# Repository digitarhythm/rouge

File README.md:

# TReK Rouge
Analog joystick macropad with RP2040-Zero.

[Firmware repository](https://github.com/digitarhythm/vial-qmk/tree/digitarhythm/keyboards/trek/rouge)

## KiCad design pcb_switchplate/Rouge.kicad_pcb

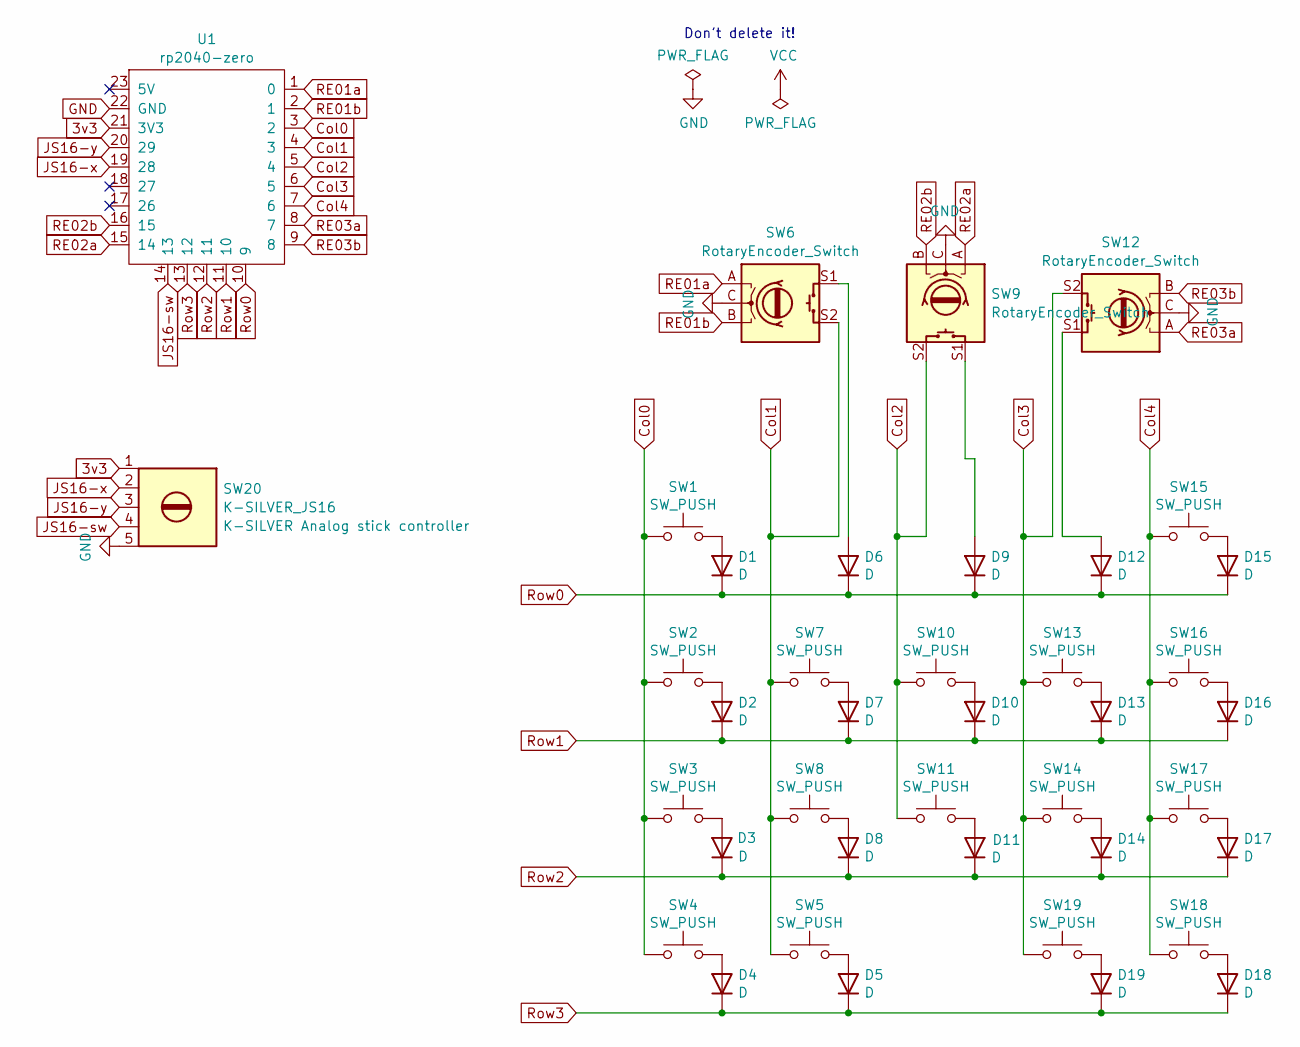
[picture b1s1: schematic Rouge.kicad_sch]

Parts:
D1, D2, D3, D4, D5, D6, D7, D8, D9, D10, D11, D12, D13, D14, D15, D16, D17, D18, D19: D; Diode_SMD
SW1, SW2, SW3, SW4, SW5, SW7, SW8, SW10, SW11, SW13, SW14, SW15, SW16, SW17, SW18, SW19: SW_PUSH; Lofree_Hotswap_1u(short_pad)
SW6, SW9, SW12: RotaryEncoder_Switch; RotaryEncoder_EC12E
SW20: K-SILVER_JS16; JS16
U1: rp2040-zero; rp2040-zero_rev(THonly)

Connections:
3v3: SW20.1, U1.21 (3V3)
Col0: SW1.1, SW2.1, SW3.1, SW4.1, U1.3 (2)
Col2: SW9.S2, SW10.1, SW11.1, U1.5 (4)
Col3: SW12.S2, SW13.1, SW14.1, SW19.1, U1.6 (5)
Col4: SW15.1, SW16.1, SW17.1, SW18.1, U1.7 (6)
GND: SW6.C, SW9.C, SW12.C, SW20.5, U1.22 (GND)
JS16-sw: SW20.4, U1.14 (13)
JS16-x: SW20.2, U1.19 (28)
JS16-y: SW20.3, U1.20 (29)
unnamed: D1.2 (A), SW1.2
unnamed: D2.2 (A), SW2.2
unnamed: D3.2 (A), SW3.2
unnamed: D4.2 (A), SW4.2
unnamed: D5.2 (A), SW5.2
unnamed: D6.2 (A), SW6.S1
unnamed: D7.2 (A), SW7.2
unnamed: D9.2 (A), SW9.S1
unnamed: D10.2 (A), SW10.2
unnamed: D11.2 (A), SW11.2
unnamed: D12.2 (A), SW12.S1
unnamed: D13.2 (A), SW13.2
unnamed: D14.2 (A), SW14.2
unnamed: D15.2 (A), SW15.2
unnamed: D16.2 (A), SW16.2
unnamed: D17.2 (A), SW17.2
unnamed: D18.2 (A), SW18.2
unnamed: D19.2 (A), SW19.2
RE01a: SW6.A, U1.1 (0)
RE01b: SW6.B, U1.2 (1)
RE02a: SW9.A, U1.15 (14)
RE02b: SW9.B, U1.16 (15)
RE03a: SW12.A, U1.8 (7)
RE03b: SW12.B, U1.9 (8)
Row0: D1.1 (K), D6.1 (K), D9.1 (K), D12.1 (K), D15.1 (K), U1.10 (9)
Row1: D2.1 (K), D7.1 (K), D10.1 (K), D13.1 (K), D16.1 (K), U1.11 (10)
Row2: D3.1 (K), D8.1 (K), D11.1 (K), D14.1 (K), D17.1 (K), U1.12 (11)
Row3: D4.1 (K), D5.1 (K), D18.1 (K), D19.1 (K), U1.13 (12)

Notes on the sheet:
Don't delete it!

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
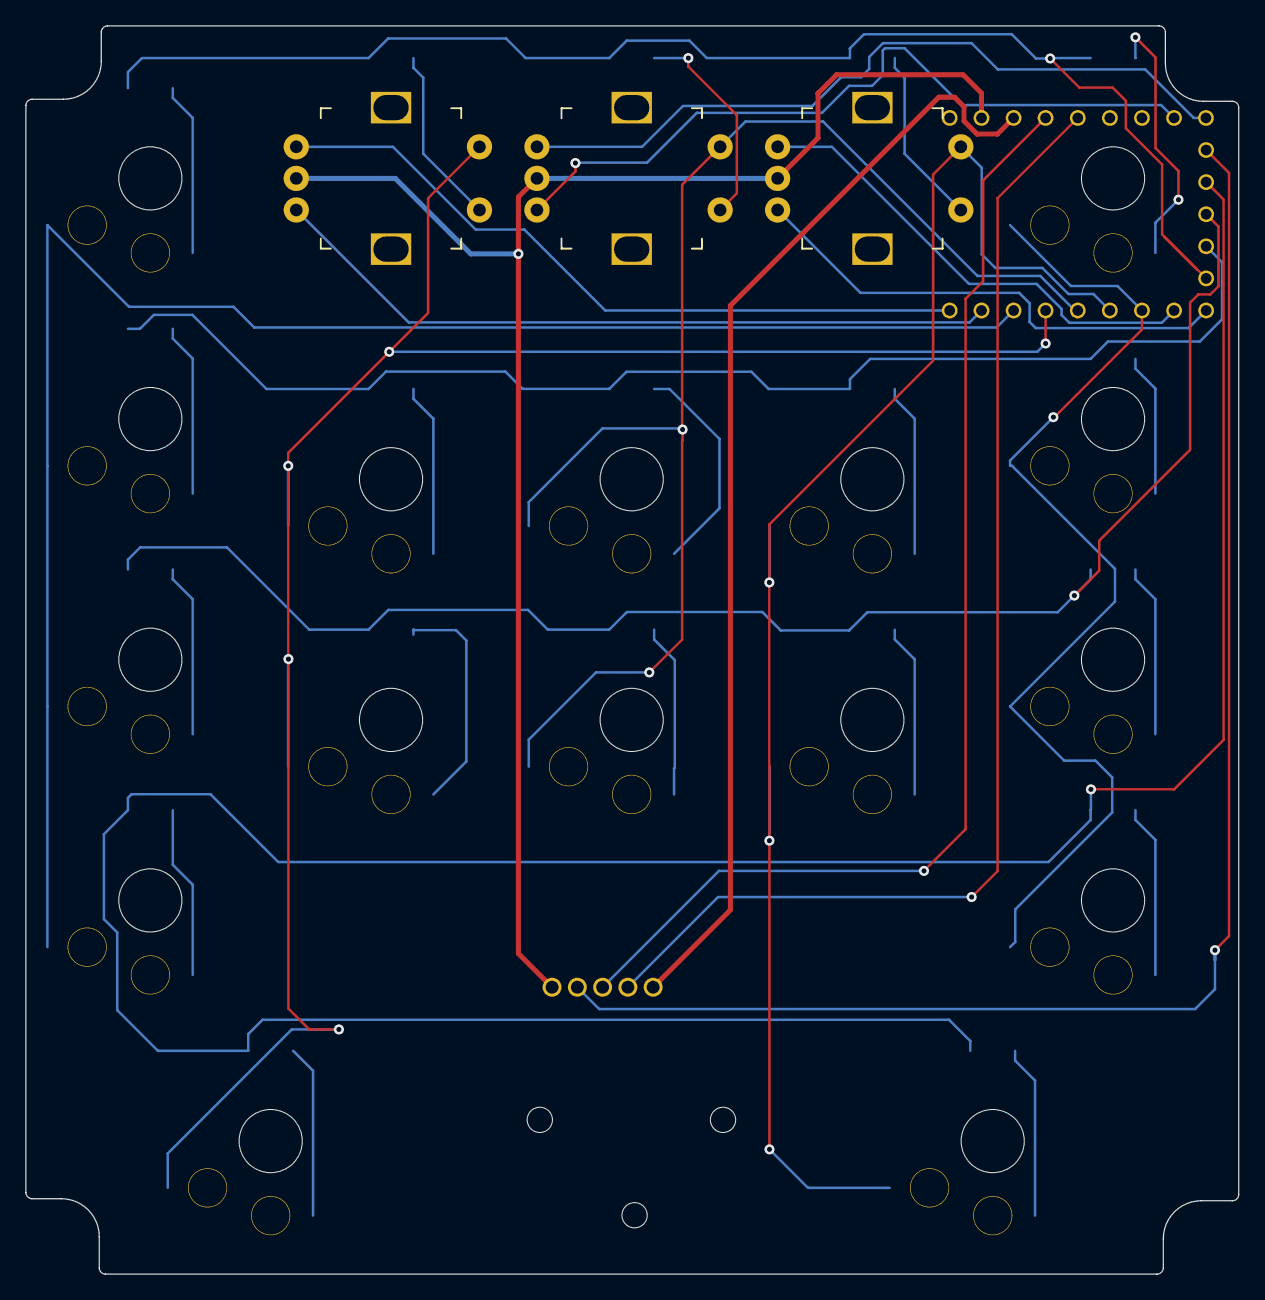
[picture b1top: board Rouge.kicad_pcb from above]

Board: 2 copper layers, 96.0 x 98.8 mm, 40 parts (1 on the bottom side), 39 nets.

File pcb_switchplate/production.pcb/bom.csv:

Designator,Footprint,Quantity,Value,LCSC Part #
"D1, D10, D11, D12, D13, D14, D15, D16, D17, D18, D19, D2, D3, D4, D5, D6, D7, D8, D9",Diode_SMD,19,D,C109203
"SW1, SW10, SW11, SW13, SW14, SW15, SW16, SW17, SW18, SW19, SW2, SW3, SW4, SW5, SW7, SW8",Lofree_Hotswap_1u(short_pad),16,SW_PUSH,
"SW12, SW6, SW9",RotaryEncoder_EC12E,3,RotaryEncoder_Switch,
SW20,K-SILVER JS16,1,K-SILVER_JS16,
U1,rp2040-zero_rev(THonly),1,rp2040-zero,

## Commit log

2026-05-21 Update firmware url
